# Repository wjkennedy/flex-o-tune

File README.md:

# FlexOTune prototype (Revision A)

This KiCad project begins the physical/visual flex-PCB experiment described in
[`flexotune.md`](flexotune.md). It favors a hand-assemblable, manufacturable
geometry prototype over final audio or power performance.

## Baseline configuration

- Variant A: continuous, straight LED flex strip for wrapping an instrument edge.
- Electronics island: 30 × 40 mm, intended for a local stiffener.
- Flex neck: 10 × 45 mm; no components or vias; initial bend target: R ≥ 5 mm.
- LED tail: 11 × 64 mm, 13 positions at 5 mm pitch, with a distinct centre.
- Provisional controller: RP2040 in a Raspberry Pi Pico module form factor.
- LEDs: WS2812B-2020 one-wire chain; power, ground, and data run through the tail.

## Flex fabrication intent

Request a two-layer polyimide flex construction with coverlay and rolled-annealed
copper where available. The island receives a local stiffener; the neck does not.
Avoid copper pours, vias, and component pads in the neck. Confirm final stackup,
coverlay openings, stiffener material/thickness, and minimum bend radius with the
selected fabricator before ordering.

## Schematic status

`FlexOTune.kicad_sch` contains USB-C sink resistors, MCP73831 LiPo charging,
an RP2040 Pico-module placeholder, two buttons, and a 13-device WS2812B-2020
data chain. The piezo input now includes a 1 MΩ series protector, rail clamps,
AC coupling, a 1.65 V bias, an MCP6001 unity-gain buffer, and an ADC isolation/
filter network.

The USB-C VBUS sink is explicitly flagged as a power source for ERC. ERC now
has zero errors. Its remaining warnings are schematic-grid artifacts from the
MCP integration and one intentionally unused end-of-chain LED output.

## Open decisions

- Final LED package/current limit and whether the tail itself is stiffened.
- Exact instrument-specific mechanical attachment and trim tabs.
- Final RP2040 integration footprint and programming method.
- Final LiPo protection, charging current, and USB data requirements.
- Piezo front-end clamp/current values after instrument testing.
# flex-o-tune

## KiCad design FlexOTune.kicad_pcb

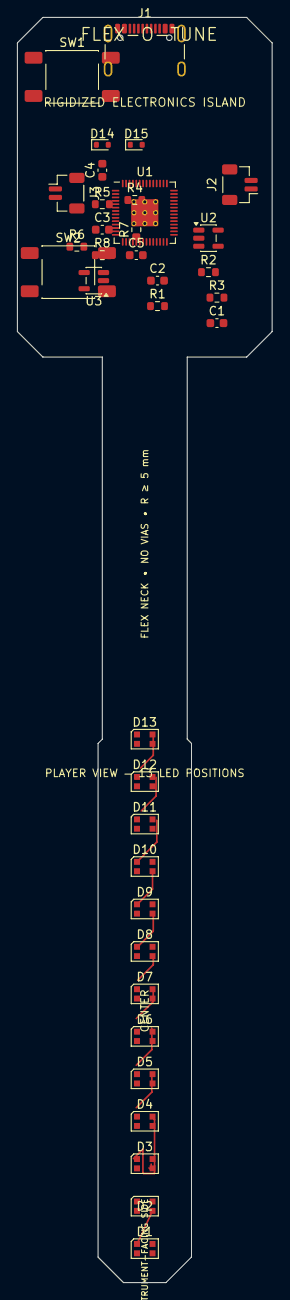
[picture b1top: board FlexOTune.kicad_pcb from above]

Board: 2 copper layers, 30.0 x 149.0 mm, 36 parts (0 on the bottom side), 28 nets.

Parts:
C1, C2: 1u 6.3V; C_0603_1608Metric
C3: 1u VREF filter; C_0603_1608Metric
C4: 100n piezo AC coupling; C_0603_1608Metric
C5: 1n ADC filter; C_0603_1608Metric
D1, D2, D3, D4, D5, D6, D7, D8, D9, D10, D11, D12, D13: WS2812B-2020; LED_WS2812B-2020_PLCC4_2.0x2.0mm
D14: BAV199 clamp low; D_SOD-523
D15: BAV199 clamp high; D_SOD-523
J1: USB-C power input; USB_C_Receptacle_GCT_USB4105-xx-A_16P_TopMnt_Horizontal
J2: LiPo battery; JST_SH_BM02B-SRSS-TB_1x02-1MP_P1.00mm_Vertical
J3: Piezo sensor; JST_SH_BM02B-SRSS-TB_1x02-1MP_P1.00mm_Vertical
R1: 5.1k CC1; R_0603_1608Metric
R2: 5.1k CC2; R_0603_1608Metric
R3: 2k charge set; R_0603_1608Metric
R4: 100R piezo input; R_0603_1608Metric
R5: 1M VREF upper; R_0603_1608Metric
R6: 1M VREF lower; R_0603_1608Metric
R7: 1M piezo bias; R_0603_1608Metric
R8: 1k ADC isolate; R_0603_1608Metric
SW1: POWER / WAKE; SW_Push_1P1T_NO_E-Switch_TL3301NxxxxxG
SW2: MODE / CAL; SW_Push_1P1T_NO_E-Switch_TL3301NxxxxxG
U1: RP2040; RP2040-QFN-56
U2: MCP73831-2-OT; SOT-23-5
U3: MCP6001 piezo buffer; SOT-23-5

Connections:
3V3: D1.4 (VDD), D2.4 (VDD), D3.4 (VDD), D4.4 (VDD), D5.4 (VDD), D6.4 (VDD), D7.4 (VDD), D8.4 (VDD), D9.4 (VDD), D10.4 (VDD), D11.4 (VDD), D12.4 (VDD), D13.4 (VDD), D15.1, R5.1, U1.35, U1.36, U3.5
BTN_MODE: SW2.1, U1.5
BTN_POWER: SW1.1, U1.4
CC1: J1.A5 (CC1), R1.1
CC2: J1.B5 (CC2), R2.1
CHG_PROG: R3.1, U2.5 (PROG)
GND: C1.2, C2.2, C3.2, C5.2, D1.2 (VSS), D2.2 (VSS), D3.2 (VSS), D4.2 (VSS), D5.2 (VSS), D6.2 (VSS), D7.2 (VSS), D8.2 (VSS), D9.2 (VSS), D10.2 (VSS), D11.2 (VSS), D12.2 (VSS), D13.2 (VSS), D14.2, J1.A1 (GND), J1.A12 (GND), J1.B1 (GND), J1.B12 (GND), J1.SH (SHIELD), J2.2, J3.2, R1.2, R2.2, R3.2, R6.2, SW1.2, SW2.2, U1.3, U1.8, U1.13, U1.18, U1.23, U1.28, U1.38, U2.2 (V_{SS}), U3.2
LED_D1: D1.1 (DOUT), D2.3 (DIN)
LED_D2: D2.1 (DOUT), D3.3 (DIN)
LED_D3: D3.1 (DOUT), D4.3 (DIN)
LED_D4: D4.1 (DOUT), D5.3 (DIN)
LED_D5: D5.1 (DOUT), D6.3 (DIN)
LED_D6: D6.1 (DOUT), D7.3 (DIN)
LED_D7: D7.1 (DOUT), D8.3 (DIN)
LED_D8: D8.1 (DOUT), D9.3 (DIN)
LED_D9: D9.1 (DOUT), D10.3 (DIN)
LED_D10: D10.1 (DOUT), D11.3 (DIN)
LED_D11: D11.1 (DOUT), D12.3 (DIN)
LED_D12: D12.1 (DOUT), D13.3 (DIN)
LED_DATA: D1.3 (DIN), U1.1
PIEZO_ADC: C5.1, R8.2, U1.31
PIEZO_BIASED: C4.2, R7.1, U3.3
PIEZO_BUF: R8.1, U3.1, U3.4
PIEZO_CLAMP: C4.1, D14.1, D15.2, R4.2
PIEZO_RAW: J3.1, R4.1
VBAT: C2.1, J2.1, U1.39, U2.3 (V_{BAT})
VBUS: C1.1, J1.A4 (VBUS), J1.A9 (VBUS), J1.B4 (VBUS), J1.B9 (VBUS), U2.4 (V_{DD})
VREF_1V65: C3.1, R5.2, R6.1, R7.2
